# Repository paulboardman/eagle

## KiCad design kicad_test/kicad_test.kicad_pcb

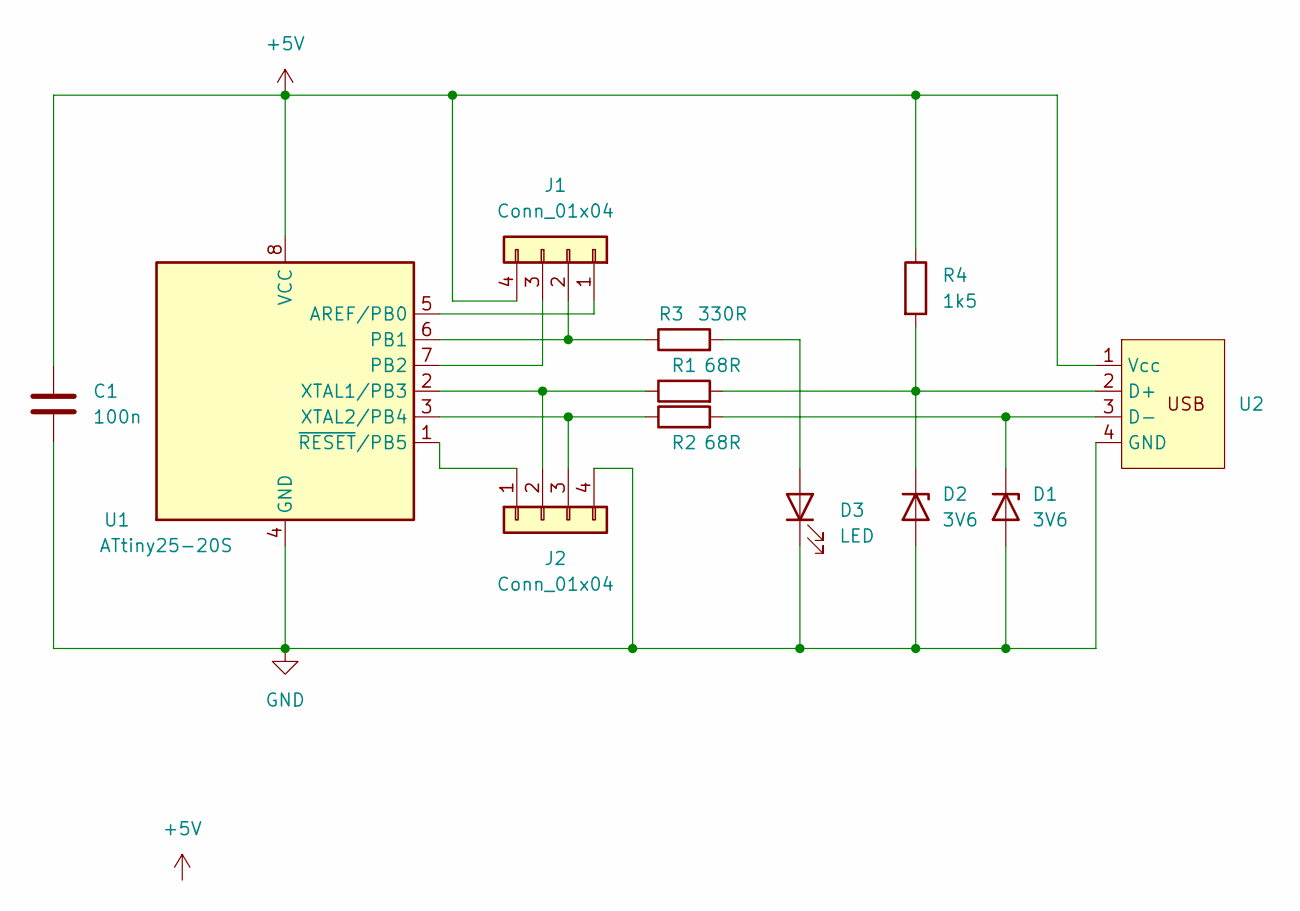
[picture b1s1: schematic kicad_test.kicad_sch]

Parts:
C1: 100n; C_1206_3216Metric_Pad1.33x1.80mm_HandSolder
D1, D2: 3V6; D_SOD-123
D3: LED; LED_1210_3225Metric_Pad1.42x2.65mm_HandSolder
J1, J2: Conn_01x04; PinHeader_1x04_P2.00mm_Vertical
R1, R2: 68R; R_0805_2012Metric_Pad1.20x1.40mm_HandSolder
R3: 330R; R_0805_2012Metric_Pad1.20x1.40mm_HandSolder
R4: 1k5; R_0805_2012Metric_Pad1.20x1.40mm_HandSolder
U1: ATtiny25-20S; SOIC-8W_5.3x5.3mm_P1.27mm
U2: PCB_USB_connector

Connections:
+5V: C1.1, J1.4, R4.1, U1.8 (VCC), U2.1 (Vcc)
GND: C1.2, D1.2 (A), D2.2 (A), D3.1 (K), J2.4, U1.4 (GND), U2.4 (GND)
unnamed: D1.1 (K), R2.2, U2.3 (D-)
unnamed: D2.1 (K), R1.2, R4.2, U2.2 (D+)
unnamed: D3.2 (A), R3.2
unnamed: J1.1, U1.5 (AREF/PB0)
unnamed: J1.2, R3.1, U1.6 (PB1)
unnamed: J1.3, U1.7 (PB2)
unnamed: J2.1, U1.1 (~RESET/PB5)
unnamed: J2.2, R1.1, U1.2 (XTAL1/PB3)
unnamed: J2.3, R2.1, U1.3 (XTAL2/PB4)

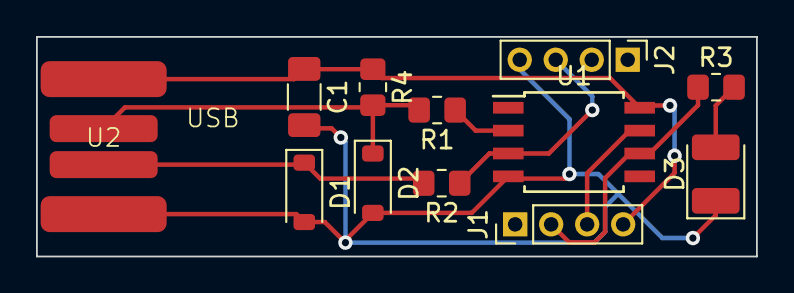
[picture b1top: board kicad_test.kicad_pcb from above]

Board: 2 copper layers, 40.0 x 12.2 mm, 12 parts (0 on the bottom side), 11 nets.

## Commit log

2014-02-23 first post
2023-06-04 testing out KiKad (7.0) instead of Eagle
